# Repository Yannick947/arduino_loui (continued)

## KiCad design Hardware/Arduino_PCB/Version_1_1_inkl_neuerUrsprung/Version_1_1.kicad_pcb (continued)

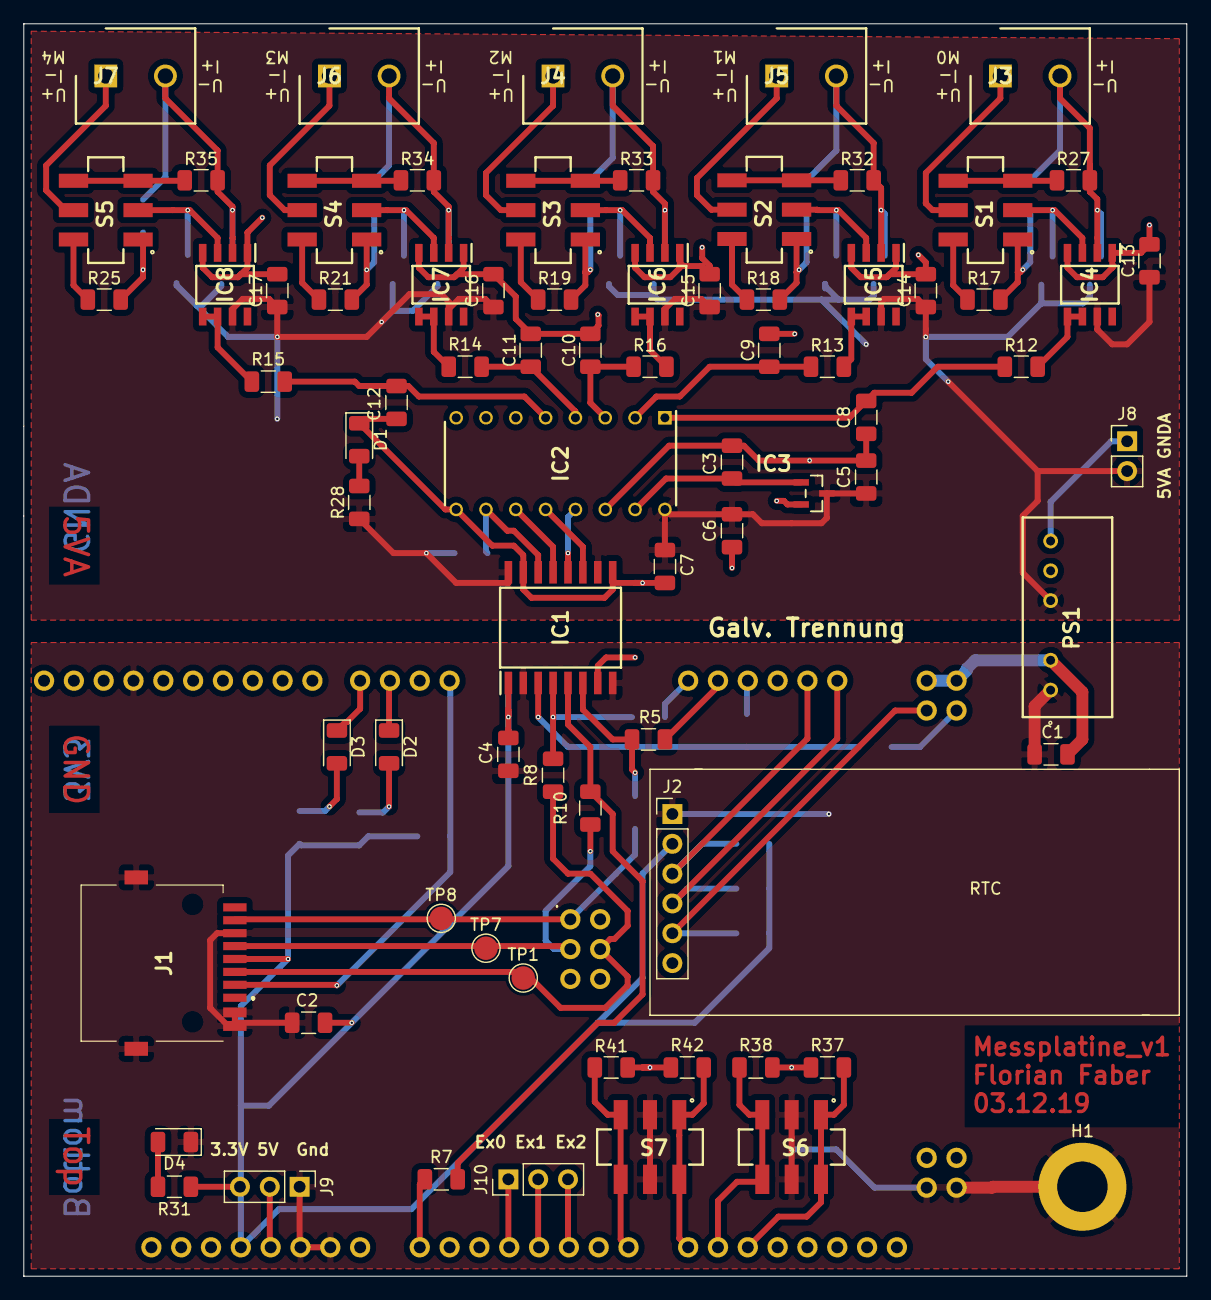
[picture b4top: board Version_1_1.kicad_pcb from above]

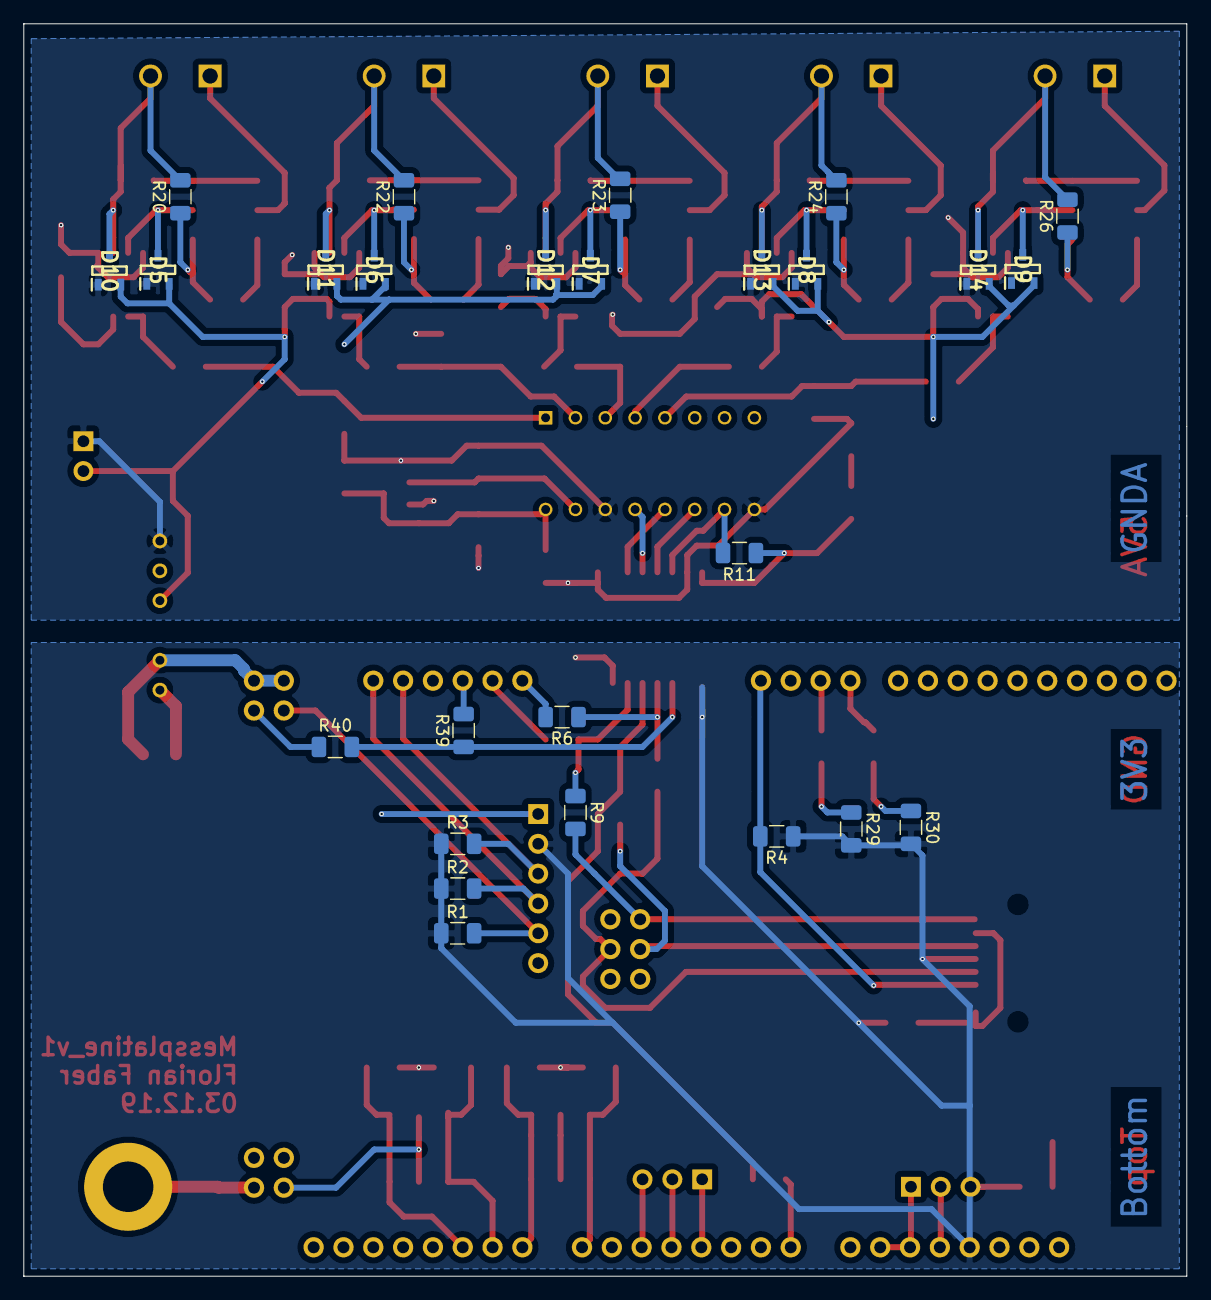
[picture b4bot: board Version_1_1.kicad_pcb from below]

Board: 2 copper layers, 99.1 x 106.7 mm, 103 parts (26 on the bottom side), 80 nets.

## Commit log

2020-07-20 Init source code
2020-07-20 Add datasheet
2020-07-20 Refactor namespace
2020-07-20 Change name to main
2020-07-20 Add photoelectric_barrier
2020-07-20 Fix folder structure
2020-07-20 - Randomvariable Audio - div. Const int
2021-09-27 Add Hardware
2021-09-28 update Display-PCB
2021-09-28 Add Klinkenadapter
2021-09-28 minor update
2021-09-29 Update DUE_Shield inkl. 3d-Modelle
2021-10-14 Ad gerber files
2021-10-20 Add gerber-file for production
2021-10-20 little update
2021-11-16 add pinmapping for v2
2021-11-16 add v1_1 change footprint of 2 switches
2021-11-24 change LED-Connection minor Layout changes
